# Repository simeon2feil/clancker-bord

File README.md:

# clancker-bord
i will try to build my own dev board
with an antena many pins and its relativly small

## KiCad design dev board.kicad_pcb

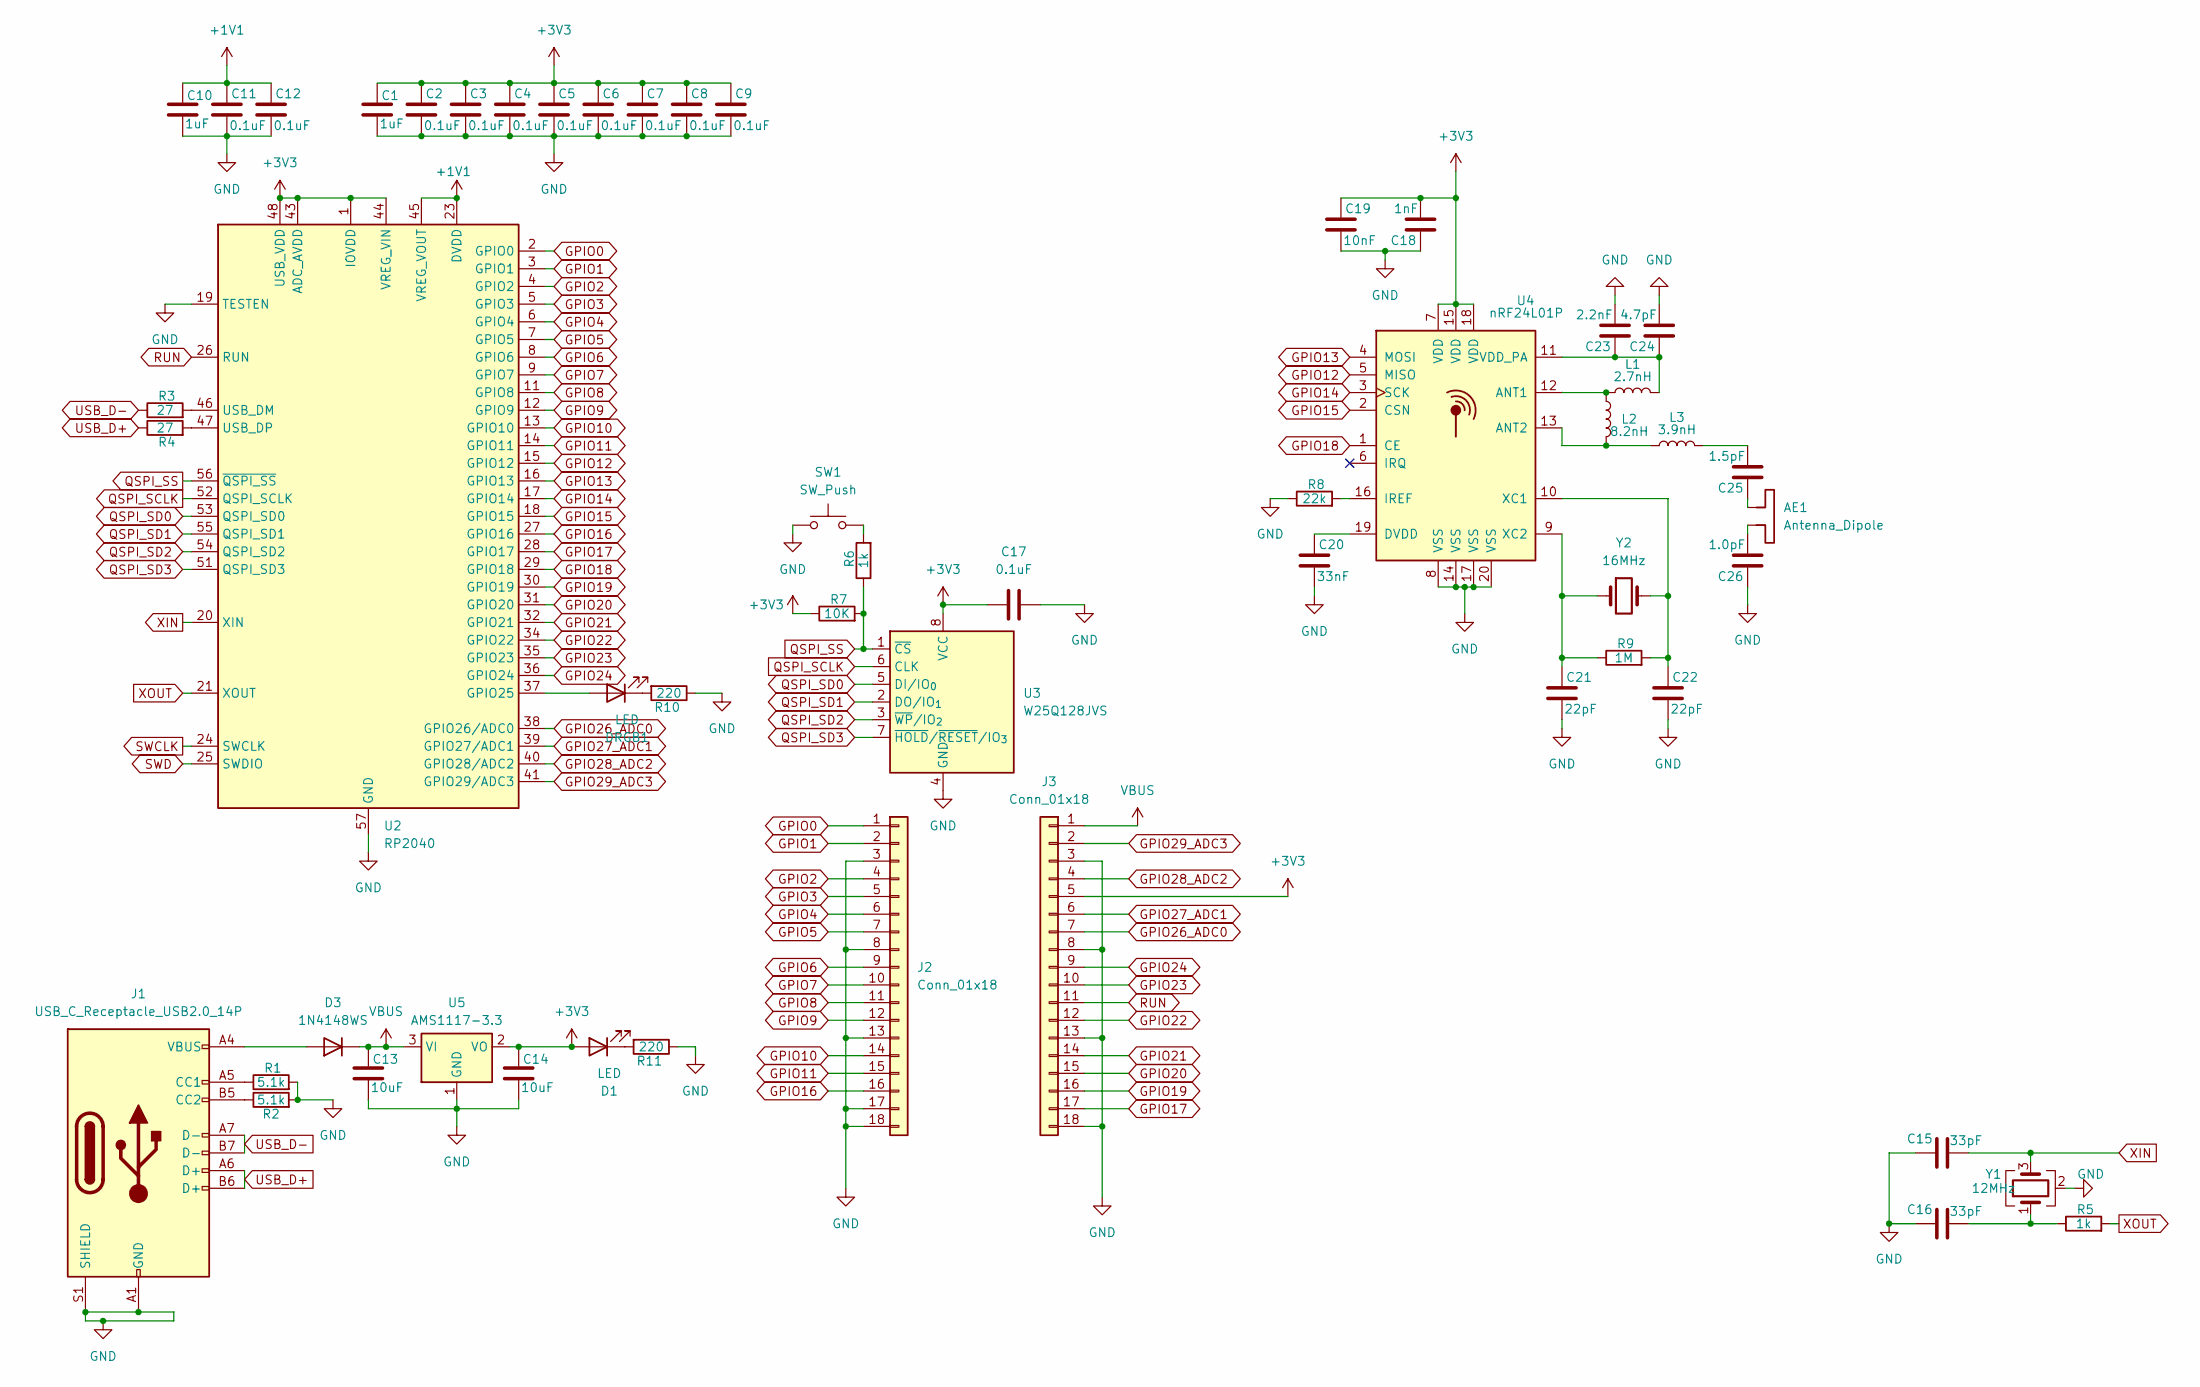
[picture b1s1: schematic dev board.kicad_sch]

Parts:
AE1: Antenna_Dipole; Texas_SWRA117D_2.4GHz_Left
C1, C10: 1uF; C_0402_1005Metric
C2, C3, C4, C5, C6, C7, C8, C9, C11, C12, C17: 0.1uF; C_0402_1005Metric
C13: 10uF; C_0603_1608Metric
C14: 10uF; C_0402_1005Metric
C15, C16: 33pF; C_0402_1005Metric
C18: 1nF; C_0402_1005Metric
C19: 10nF; C_0402_1005Metric
C20: 33nF; C_0402_1005Metric
C21, C22: 22pF; C_0402_1005Metric
C23: 2.2nF; C_0402_1005Metric
C24: 4.7pF; C_0402_1005Metric
C25: 1.5pF; C_0402_1005Metric
C26: 1.0pF; C_0402_1005Metric
D1: LED; LED_0603_1608Metric
D3: 1N4148WS; D_SOD-323
DRGB1: LED; LED_0603_1608Metric
J1: USB_C_Receptacle_USB2.0_14P; USB_C_Receptacle_HRO_TYPE-C-31-M-12
J2, J3: Conn_01x18; PinHeader_1x18_P2.54mm_Vertical
L1: 2.7nH; L_0402_1005Metric
L2: 8.2nH; L_0402_1005Metric
L3: 3.9nH; L_0402_1005Metric
R1, R2: 5.1k; R_0402_1005Metric
R3, R4: 27; R_0402_1005Metric
R5, R6: 1k; R_0402_1005Metric
R7: 10K; R_0402_1005Metric
R8: 22k; R_0402_1005Metric
R9: 1M; R_0402_1005Metric
R10, R11: 220; R_0402_1005Metric
SW1: SW_Push; SW_TS-1088-AR02016
U2: RP2040; QFN-56-1EP_7x7mm_P0.4mm_EP3.2x3.2mm
U3: W25Q128JVS; Winbond_USON-8-1EP_3x2mm_P0.5mm_EP0.2x1.6mm
U4: nRF24L01P; QFN-20-1EP_4x4mm_P0.5mm_EP2.5x2.5mm
U5: AMS1117-3.3; SOT-89-3
Y1: 12MHz; Crystal_SMD_3225-4Pin_3.2x2.5mm
Y2: 16MHz; Crystal_SMD_3225-4Pin_3.2x2.5mm

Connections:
+1V1: C10.1, C11.1, C12.1, U2.23 (DVDD), U2.45 (VREG_VOUT), U2.50 (DVDD)
+3V3: C1.1, C2.1, C3.1, C4.1, C5.1, C6.1, C7.1, C8.1, C9.1, C14.1, C17.1, C18.2, C19.1, D1.2 (A), J3.5, R7.1, U2.1 (IOVDD), U2.10 (IOVDD), U2.22 (IOVDD), U2.33 (IOVDD), U2.42 (IOVDD), U2.43 (ADC_AVDD), U2.44 (VREG_VIN), U2.48 (USB_VDD), U2.49 (IOVDD), U3.8 (VCC), U4.7 (VDD), U4.15 (VDD), U4.18 (VDD), U5.2 (VO)
GND: C1.2, C2.2, C3.2, C4.2, C5.2, C6.2, C7.2, C8.2, C9.2, C10.2, C11.2, C12.2, C13.2, C14.2, C15.1, C16.1, C17.2, C18.1, C19.2, C20.2, C21.2, C22.2, C23.2, C24.2, C26.1, J1.A1 (GND), J1.A12 (GND), J1.B1 (GND), J1.B12 (GND), J1.S1 (SHIELD), J2.3, J2.8, J2.13, J2.17, J2.18, J3.3, J3.8, J3.13, J3.18, R1.2, R2.2, R8.1, R10.1, R11.1, SW1.1, U2.19 (TESTEN), U2.57 (GND), U3.4 (GND), U4.8 (VSS), U4.14 (VSS), U4.17 (VSS), U4.20 (VSS), U5.1 (GND), Y1.2 (G), Y1.4 (G)
GPIO0: J2.1, U2.2 (GPIO0)
GPIO1: J2.2, U2.3 (GPIO1)
GPIO2: J2.4, U2.4 (GPIO2)
GPIO3: J2.5, U2.5 (GPIO3)
GPIO4: J2.6, U2.6 (GPIO4)
GPIO5: J2.7, U2.7 (GPIO5)
GPIO6: J2.9, U2.8 (GPIO6)
GPIO7: J2.10, U2.9 (GPIO7)
GPIO8: J2.11, U2.11 (GPIO8)
GPIO9: J2.12, U2.12 (GPIO9)
GPIO10: J2.14, U2.13 (GPIO10)
GPIO11: J2.15, U2.14 (GPIO11)
GPIO12: U2.15 (GPIO12), U4.5 (MISO)
GPIO13: U2.16 (GPIO13), U4.4 (MOSI)
GPIO14: U2.17 (GPIO14), U4.3 (SCK)
GPIO15: U2.18 (GPIO15), U4.2 (CSN)
GPIO16: J2.16, U2.27 (GPIO16)
GPIO17: J3.17, U2.28 (GPIO17)
GPIO18: U2.29 (GPIO18), U4.1 (CE)
GPIO19: J3.16, U2.30 (GPIO19)
GPIO20: J3.15, U2.31 (GPIO20)
GPIO21: J3.14, U2.32 (GPIO21)
GPIO22: J3.12, U2.34 (GPIO22)
GPIO23: J3.10, U2.35 (GPIO23)
GPIO24: J3.9, U2.36 (GPIO24)
GPIO26_ADC0: J3.7, U2.38 (GPIO26/ADC0)
GPIO27_ADC1: J3.6, U2.39 (GPIO27/ADC1)
GPIO28_ADC2: J3.4, U2.40 (GPIO28/ADC2)
GPIO29_ADC3: J3.2, U2.41 (GPIO29/ADC3)
unnamed: AE1.1, C25.1
unnamed: AE1.2, C26.2
unnamed: C16.2, R5.1, Y1.1
unnamed: C25.2, L3.2
unnamed: D1.1 (K), R11.2
unnamed: D3.2 (A), J1.A4 (VBUS), J1.A9 (VBUS), J1.B4 (VBUS), J1.B9 (VBUS)
unnamed: DRGB1.2 (A), U2.37 (GPIO25)
unnamed: DRGB1.1 (K), R10.2
unnamed: J1.A5 (CC1), R1.1
unnamed: J1.B5 (CC2), R2.1
unnamed: R6.2, SW1.2
unnamed: R3.2, U2.46 (USB_DM)
unnamed: R4.2, U2.47 (USB_DP)
unnamed: L1.1, L2.1, U4.12 (ANT1)
unnamed: L2.2, L3.1, U4.13 (ANT2)
unnamed: C20.1, U4.19 (DVDD)
unnamed: R8.2, U4.16 (IREF)
unnamed: C23.1, C24.1, L1.2, U4.11 (VDD_PA)
unnamed: C22.1, R9.2, U4.10 (XC1), Y2.2
unnamed: C21.1, R9.1, U4.9 (XC2), Y2.1
QSPI_SCLK: U2.52 (QSPI_SCLK), U3.6 (CLK)
QSPI_SD0: U2.53 (QSPI_SD0), U3.5 (DI/IO_{0})
QSPI_SD1: U2.55 (QSPI_SD1), U3.2 (DO/IO_{1})
QSPI_SD2: U2.54 (QSPI_SD2), U3.3 (~WP/IO_{2})
QSPI_SD3: U2.51 (QSPI_SD3), U3.7 (~HOLD/~RESET/IO_{3})
QSPI_SS: R6.1, R7.2, U2.56 (~QSPI_SS), U3.1 (~CS)
RUN: J3.11, U2.26 (RUN)
SWCLK: U2.24 (SWCLK)
SWD: U2.25 (SWDIO)
USB_D+: J1.A6 (D+), J1.B6 (D+), R4.1
USB_D-: J1.A7 (D-), J1.B7 (D-), R3.1
VBUS: C13.1, D3.1 (K), J3.1, U5.3 (VI)
XIN: C15.2, U2.20 (XIN), Y1.3
XOUT: R5.2, U2.21 (XOUT)

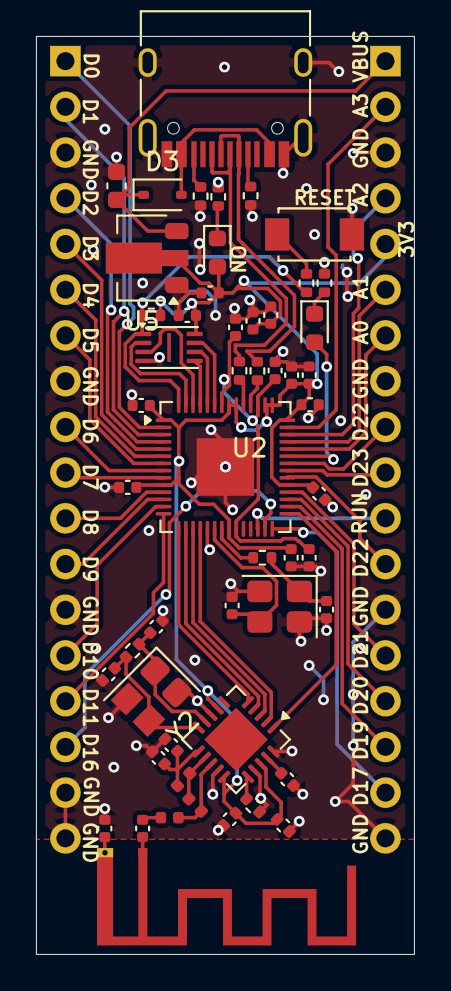
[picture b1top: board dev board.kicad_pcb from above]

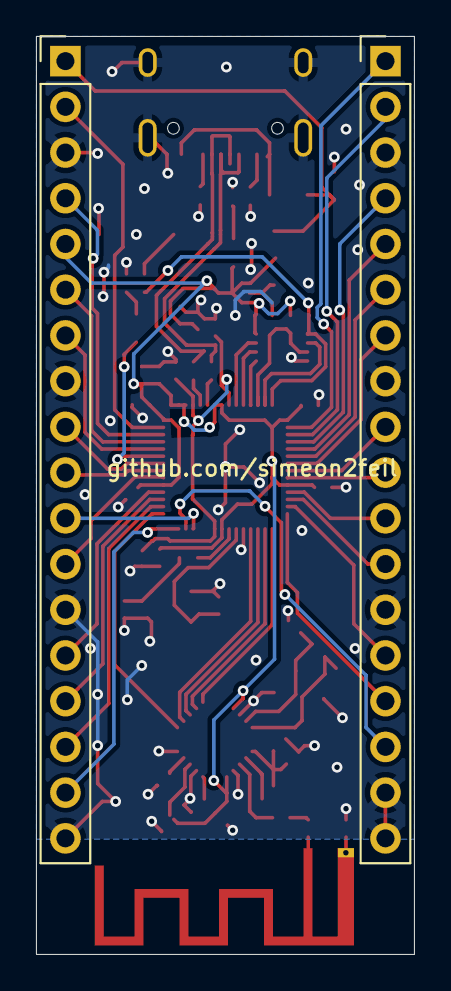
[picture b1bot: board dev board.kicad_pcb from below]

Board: 2 copper layers, 21.0 x 51.0 mm, 54 parts (2 on the bottom side), 64 nets.

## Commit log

2026-06-11 bom.cvs
